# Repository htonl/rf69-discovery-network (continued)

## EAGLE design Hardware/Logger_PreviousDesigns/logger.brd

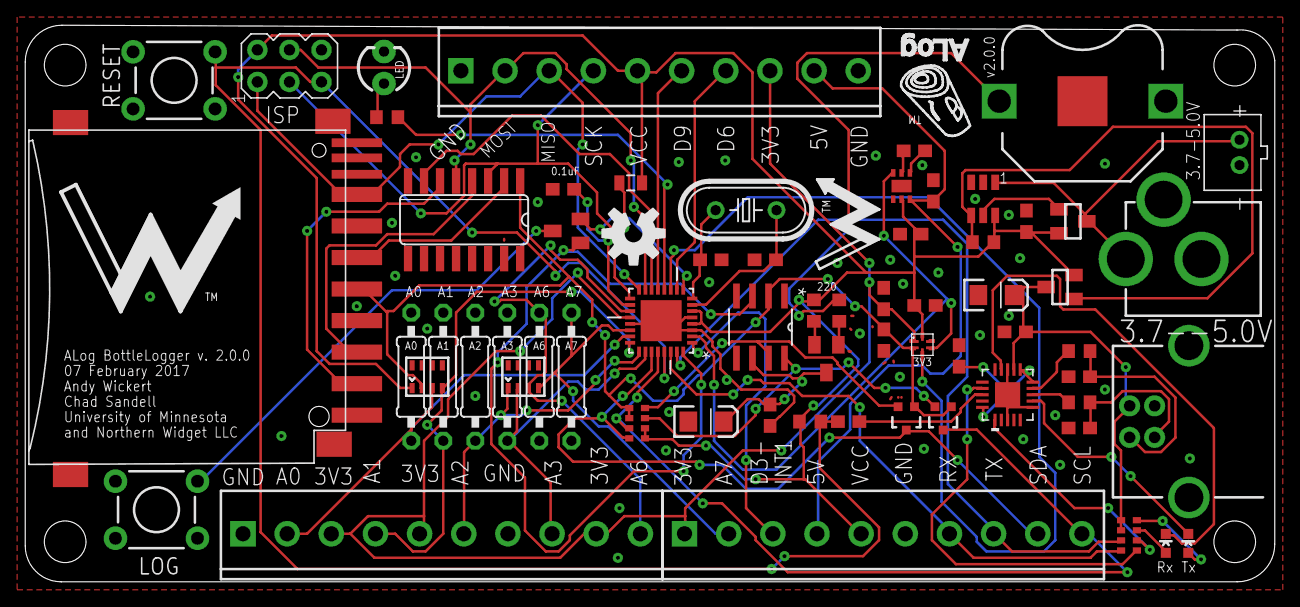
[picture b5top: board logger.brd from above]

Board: 2 copper layers, 99.0 x 44.1 mm, 73 parts (0 on the bottom side), 60 nets.

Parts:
3V3: 6-TMLF
5V_CHARGE_PUMP: 5V; SON65P200X200X80-7N
A0, A1, A2, A3, A6, A7: 0207/10
ADECOUP: 0.1uF; C0603
C1, C17: 0.1uF; C0603
C14, C15: 10nF; CECJ-1206
C21: 10uF; EIA3216
CLOCK_BATT: 3V Backup Battery; BATTCON_12MM_PTH
CLOCK_BATT_DECOUP: 0.1uF; C0603
CLOCK_BATT_DECOUPLE: 10uF; EIA3216
CLOCK_CIN1, CLOCK_CIN2, CLOCK_CIN3: 1uF; C0603
CN1: JST-PH-2-THM
COUT: 1uF; C0603
COUT1: 0.1uF; C0603
CX0, CX1, CX2, CX3: 33pF; C0603
C_BOOST_1: 4.7uF; C0603
C_BOOST_2, C_BOOST_3: 2.2uF; C0603
D1: BAT54C; SOT23C
D2: BAT54; SOT23C
D+: 27ohm; R0603
D-: 27ohm; R0603
H0, H1, H3: SCREWTERMINAL-3.5MM-8
IC1: LTC4412; TSOT23-6
ISP: AVRISP-6; AVRISP
J1: POWER_JACKPTH; POWER_JACK_PTH
JP1, JP2, JP3, JP4: STAND-OFF
JP5: USB-B; USB-B-PTH
LED: LED3MM
LED1: Yellow; LED-0603
LED2: Blue; LED-0603
LOG: LOG; TACTILE-PTH
LOGO1: OSHW-LOGOM; OSHW-LOGO-M
LSHIFT: 4050D; SO16
L_LPF: 10uH; 0805
MCU: ATMEGA328P-MU; QFN50P500X500X100-33N
Q1, Q2: FDN360P; SUPER-SOT3
Q3, Q4: 2N7002PW; SOT323
RCKL1: 220; R0603
RCLK2: 220; R0603
RESET: Reset; TACTILE-PTH
RN1: 1K; 0603-ARC
RN2: 3.3K; 0603-ARC
RSTAT: 470k; R0603
R_LED: 220; R0603
R_RESET: 10k; R0603
SD: SDMMC06132; 06132
U1: DS3231MZ/V+T; 21-0041B_8
U2: FT231X-Q; QFN20
U$1: NWLOGO
U$2: ALOG_LOGO_V1_5.5MM; ALOG_LOGO_V1_SMALL
U$3: NWLOGO_MED
U$9: ALOG-BACKSILK-2.0
XTAL: 8MHz; HC49U-V

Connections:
5V: 5V_CHARGE_PUMP.3, C_BOOST_3.2, H1.4, H3.9
+3V3: 3V3.1, CLOCK_CIN2.1, H0.3, H0.5, H0.9, H1.1, H3.8, MCU.20
A0: A0.2, C14.C1, H0.2, MCU.23
A1: A1.2, C14.D1, H0.4, MCU.24
A2: A2.2, C15.A1, H0.6, MCU.25
A3: A3.2, C15.B1, H0.8, MCU.26
A6: A6.1, C15.C1, H0.10, MCU.19
A7: A7.1, C15.D1, H1.2, MCU.22
AVCC: ADECOUP.1, L_LPF.2, MCU.18
BAT: CLOCK_BATT_DECOUP.1, CLOCK_BATT_DECOUPLE.A, D1.3, U1.6
CLK: H3.4, ISP.3, LSHIFT.3, MCU.17
CS-SD: LSHIFT.7, MCU.14
D3-INT1: H1.3, MCU.1
D4-SENSE_LDO_SWITCH: 3V3.4, 5V_CHARGE_PUMP.6, MCU.2
D5_MANUAL_LOG: D2.2, MCU.9
D6-EXT: H3.7, MCU.10
D7-CLOCK_SD_SWITCH: 3V3.3, MCU.11
D8_LED: MCU.12, R_LED.1
D9-CS-EXT: H3.6, MCU.13
DI: H3.2, ISP.4, LSHIFT.5, MCU.15
DO: H3.3, ISP.1, MCU.16, SD.7
DTR: COUT1.1, U2.18
GND: 3V3.5, 5V_CHARGE_PUMP.1, 5V_CHARGE_PUMP.7, A0.1, A1.1, A2.1, A3.1, A6.2, A7.2, ADECOUP.2, C1.2, C14.A2, C14.B2, C14.C2, C14.D2, C15.A2, C15.B2, C15.C2, C15.D2, C17.2, C21.C, CLOCK_BATT.GND, CLOCK_BATT_DECOUP.2, CLOCK_BATT_DECOUPLE.C, CLOCK_CIN1.2, CLOCK_CIN2.2, CLOCK_CIN3.2, CN1.2, COUT.2, CX0.1, CX1.1, CX2.1, CX3.1, C_BOOST_1.1, C_BOOST_3.1, H0.1, H0.7, H1.6, H3.1, H3.10, IC1.2, IC1.3, ISP.6, J1.GND, J1.GNDBREAK, JP5.GND, LED.K, LOG.1, LSHIFT.8, LSHIFT.9, LSHIFT.11, LSHIFT.14, MCU.3, MCU.5, MCU.21, MCU.33, RESET.1, SD.3, SD.6, SD.GP, SD.GP3, U1.5, U2.3, U2.6, U2.13, U2.21
INT0: D2.1, MCU.32, U1.3
LED+: LED.A, R_LED.2
unnamed: D1.1, RCLK2.1
unnamed: CLOCK_BATT.VCC@1, RCLK2.2
unnamed: CX3.2, D+.2, JP5.D+
unnamed: CX2.2, D-.2, JP5.D-
unnamed: LED2.A, RN1.4
unnamed: LED2.C, U2.7
unnamed: IC1.4, Q2.1, RSTAT.1
unnamed: IC1.5, Q1.1
unnamed: LED1.A, RN1.3
unnamed: LED1.C, U2.14
unnamed: D2.3, LOG.3
unnamed: D-.1, U2.9
unnamed: 5V_CHARGE_PUMP.4, C_BOOST_2.2
unnamed: 5V_CHARGE_PUMP.5, C_BOOST_2.1
unnamed: D+.1, U2.8
unnamed: C1.1, U2.10, U2.11, U2.20
unnamed: RN1.1, U2.17
unnamed: RN1.2, U2.1
unnamed: D1.2, RCKL1.1
RESET: COUT1.2, ISP.5, MCU.29, RESET.3, R_RESET.1
RX-I: H1.7, MCU.30, RN1.8
SCL: H1.10, MCU.28, Q4.3, RN2.7
SCL_3V3: Q4.2, RN2.3, U1.8
SDA: H1.9, MCU.27, Q3.3, RN2.8
SDA_3V3: Q3.2, RN2.4, U1.7
SD_CLK: LSHIFT.2, SD.5
SD_CS: LSHIFT.6, SD.1
SD_DI: LSHIFT.4, SD.2
TX-O: H1.8, MCU.31, RN1.7
VBAT: CN1.1, IC1.1, J1.PWR, Q1.3
VCC: 3V3.6, 5V_CHARGE_PUMP.2, C14.A1, CLOCK_CIN1.1, COUT.1, C_BOOST_1.2, H1.5, H3.5, IC1.6, ISP.2, L_LPF.1, MCU.4, MCU.6, Q1.2, Q2.2, RCKL1.2, RN2.1, RN2.2, RSTAT.2, R_RESET.2
VDD: 3V3.2, C14.B1, CLOCK_CIN3.1, LSHIFT.1, Q3.1, Q4.1, RN2.5, RN2.6, SD.4, U1.2
VUSB: C17.1, C21.A, JP5.VBUS, Q2.3, RN1.5, RN1.6, U2.12
X0: CX0.2, MCU.7, XTAL.2
X1: CX1.2, MCU.8, XTAL.1

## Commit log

2017-05-03 Adding the code
2017-05-03 Added files
2017-05-03 Organization
2017-05-03 More organization
2017-05-03 Jeff changes
2017-05-03 organization stuff
2017-05-03 readme additions
2017-05-03 More Readme edits
2017-05-03 Final changes
2017-05-04 some edits
